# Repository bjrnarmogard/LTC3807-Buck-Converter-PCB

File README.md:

# LTC3807 Synchronous Buck Converter (5V to 1V, 3A) – Simulation and PCB Design

This repository contains the complete circuit simulation in **LTspice**, schematic capture, 2-layer PCB layout in **KiCad**, as well as full manufacturing files and documentation for a synchronous step-down (buck) power supply based on the **LTC3807EFE** controller.

## Technical Specifications
* **Controller IC:** Analog Devices LTC3807EFE
* **Input Voltage:** 5V DC
* **Output Voltage / Current:** 1V DC / 3A
* **PCB Stackup:** 2-layer PCB (`F.Cu` and `B.Cu`) featuring a solid ground plane (`GND`) on the bottom layer for optimal EMC shielding and low return-path inductance
* **Verification Status:** Passed KiCad Design Rule Check (DRC) with 0 errors and 0 warnings

## Repository Structure and Contents
* **`LTspice/`** – Simulation files (`Buck_converter_5V_til_1V_3A.asc` and `.plt` plot settings) used to verify output voltage regulation and ripple prior to PCB layout.
* **`Levering/`** – Complete manufacturing and documentation deliverables:
  * **`1_Kortet_i_3D.pdf`** – 3D renders of the top and bottom sides of the finished PCB.
  * **`2_Samledokument.pdf`** – Combined documentation package including the schematic, 2D PCB layout, DRC report (0 errors and 0 warnings), and Bill of Materials.
  * **`Gerber/`** – Manufacturing Gerber files in Protel format (`.gtl`, `.gbl`, `.gko`, `.gts`, `.gbs`, `.gto`, `.gbo`).
  * **`NC Drill/`** – Excellon drill file (`.TXT`).
  * **`BOM/`** – Complete Bill of Materials in Excel (`.xlsx`) calculated for 4 boards with DigiKey part numbers.
* **KiCad Project Files (`TLC3807_prosjekt.*`)** – Complete source files for the schematic (`.kicad_sch`), PCB layout (`.kicad_pcb`), and project configuration (`.kicad_pro`).

---
*Designed and documented by Bjørnar Mogård.*

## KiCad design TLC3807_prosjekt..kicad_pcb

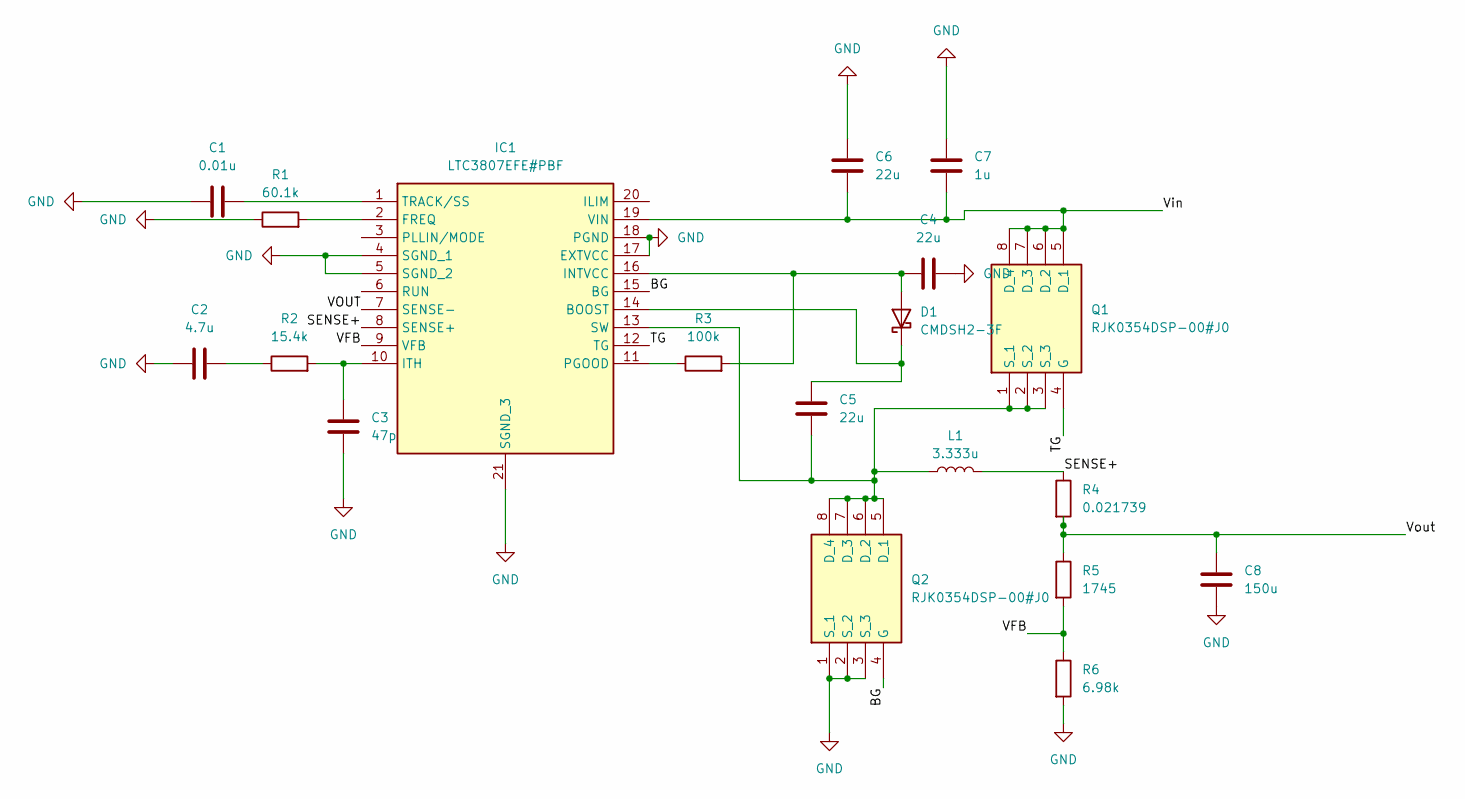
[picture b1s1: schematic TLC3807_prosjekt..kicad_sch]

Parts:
C1: 0.01u; C_1206_3216Metric
C2: 4.7u; C_1206_3216Metric
C3: 47p; C_1206_3216Metric
C4, C5, C6: 22u; C_1206_3216Metric
C7: 1u; C_1206_3216Metric
C8: 150u; C_1206_3216Metric
D1: CMDSH2-3F; LED_SK6805_PLCC4_2.4x2.7mm_P1.3mm
IC1: LTC3807EFE#PBF; TSSOP-20-1EP_4.4x6.5mm_P0.65mm_EP2.15x3.35mm; Manufacturer_Part_Number LTC3807EFE#PBF; Mouser Part Number 584-LTC3807EFE#PBF
L1: 3.333u; L_6.3x6.3_H3
Q1, Q2: RJK0354DSP-00#J0; SOIC-8_3.9x4.9mm_P1.27mm; Mouser Part Number 968-RJK0354DSP-00#J0
R1: 60.1k; R_1206_3216Metric
R2: 15.4k; R_1206_3216Metric
R3: 100k; R_1206_3216Metric
R4: 0.021739; R_1206_3216Metric
R5: 1745; R_1206_3216Metric
R6: 6.98k; R_1206_3216Metric

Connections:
/BG: IC1.15 (BG), Q2.4 (G)
/SENSE+: IC1.8 (SENSE+), L1.2, R4.1
/TG: IC1.12 (TG), Q1.4 (G)
/VFB: IC1.9 (VFB), R5.2, R6.1
/VOUT: C8.1, IC1.7 (SENSE-), R4.2, R5.1
/Vin: C6.2, C7.2, IC1.19 (VIN), Q1.5 (D_1), Q1.6 (D_2), Q1.7 (D_3), Q1.8 (D_4)
GND: C1.1, C2.1, C3.1, C4.2, C6.1, C7.1, C8.2, IC1.4 (SGND_1), IC1.5 (SGND_2), IC1.17 (EXTVCC), IC1.18 (PGND), IC1.21 (SGND_3), Q2.1 (S_1), Q2.2 (S_2), Q2.3 (S_3), R1.1, R6.2
unnamed: C2.2, R2.1
unnamed: C4.1, D1.2 (A), IC1.16 (INTVCC), R3.2
unnamed: C5.1, D1.1 (K), IC1.14 (BOOST)
unnamed: IC1.2 (FREQ), R1.2
unnamed: C3.2, IC1.10 (ITH), R2.2
unnamed: IC1.11 (PGOOD), R3.1
unnamed: C5.2, IC1.13 (SW), L1.1, Q1.1 (S_1), Q1.2 (S_2), Q1.3 (S_3), Q2.5 (D_1), Q2.6 (D_2), Q2.7 (D_3), Q2.8 (D_4)
unnamed: C1.2, IC1.1 (TRACK/SS)

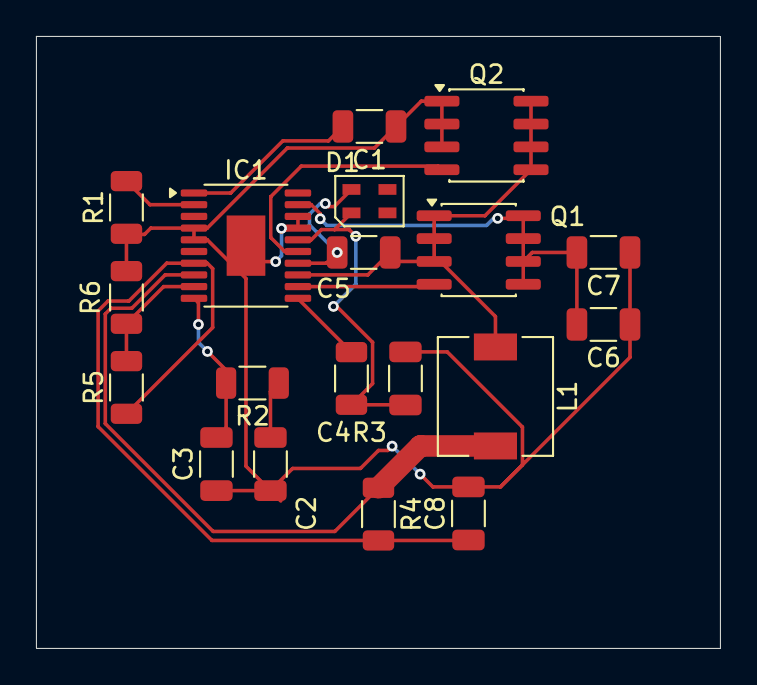
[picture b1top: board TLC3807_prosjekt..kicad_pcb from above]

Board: 2 copper layers, 38.0 x 34.0 mm, 19 parts (0 on the bottom side), 15 nets.
